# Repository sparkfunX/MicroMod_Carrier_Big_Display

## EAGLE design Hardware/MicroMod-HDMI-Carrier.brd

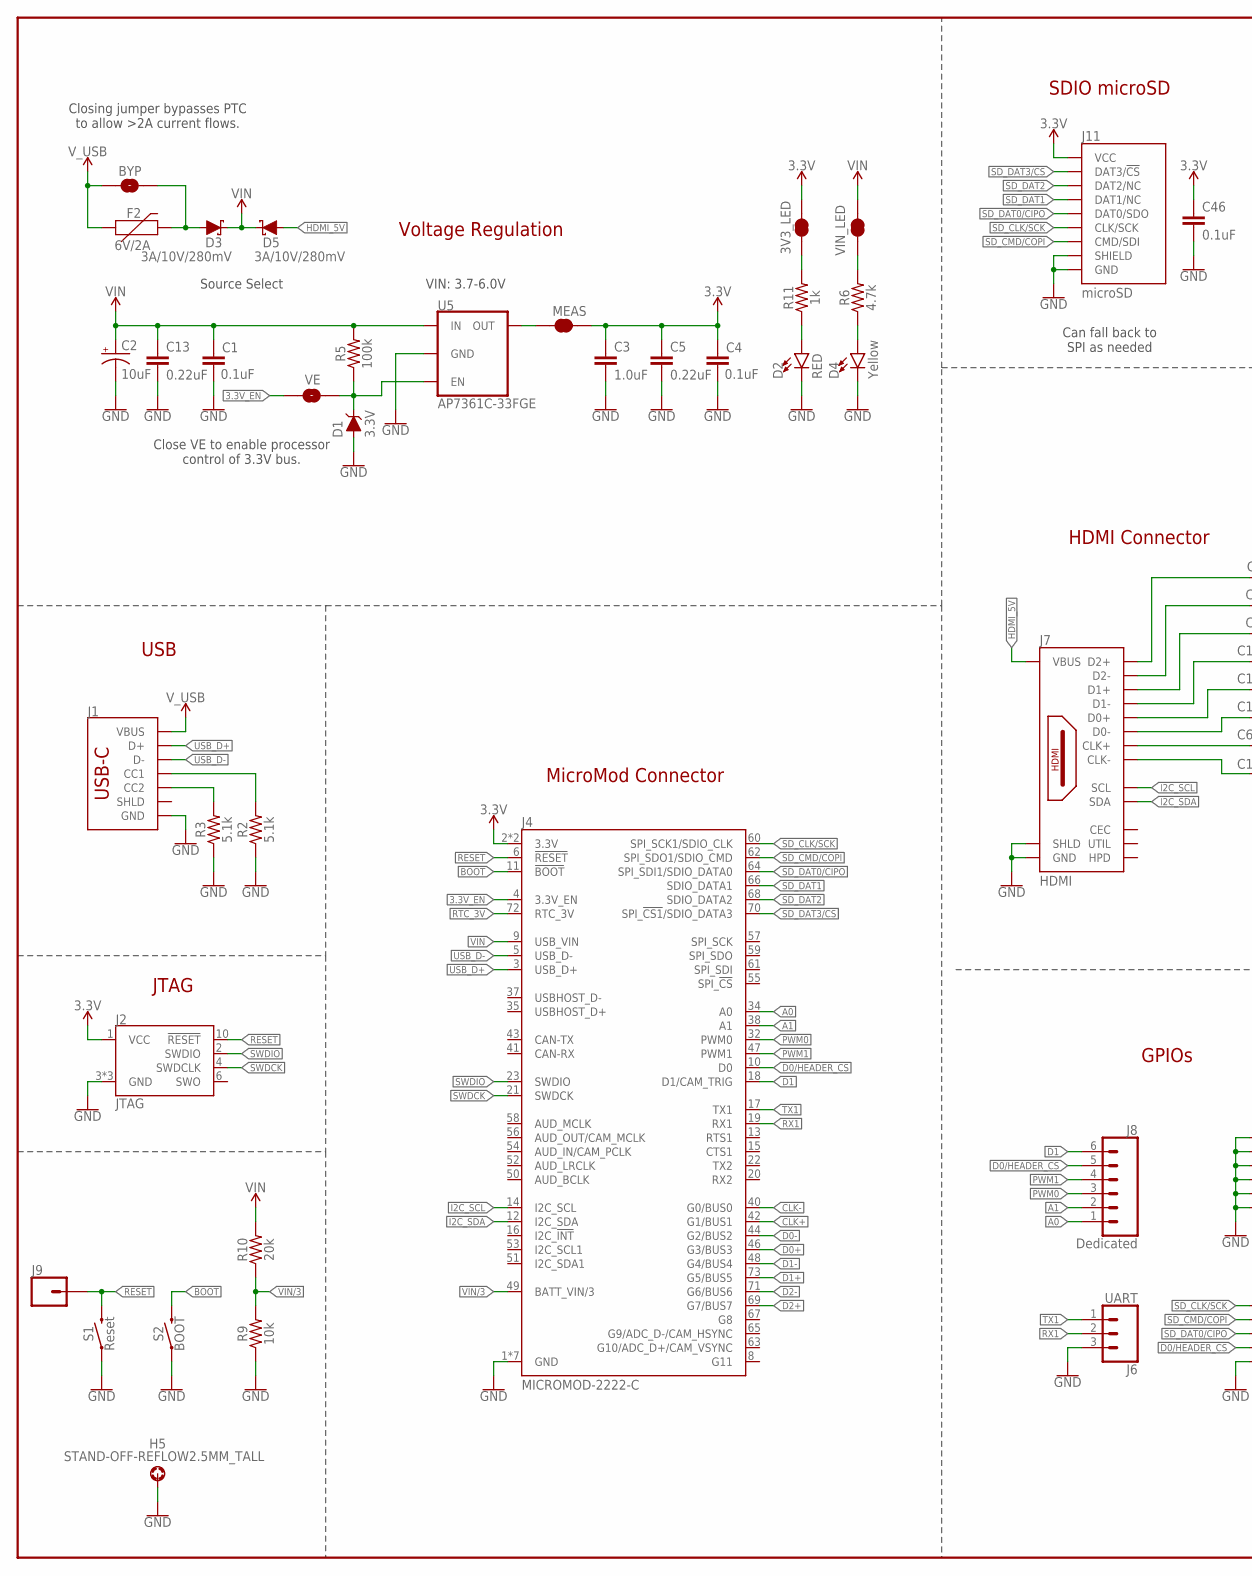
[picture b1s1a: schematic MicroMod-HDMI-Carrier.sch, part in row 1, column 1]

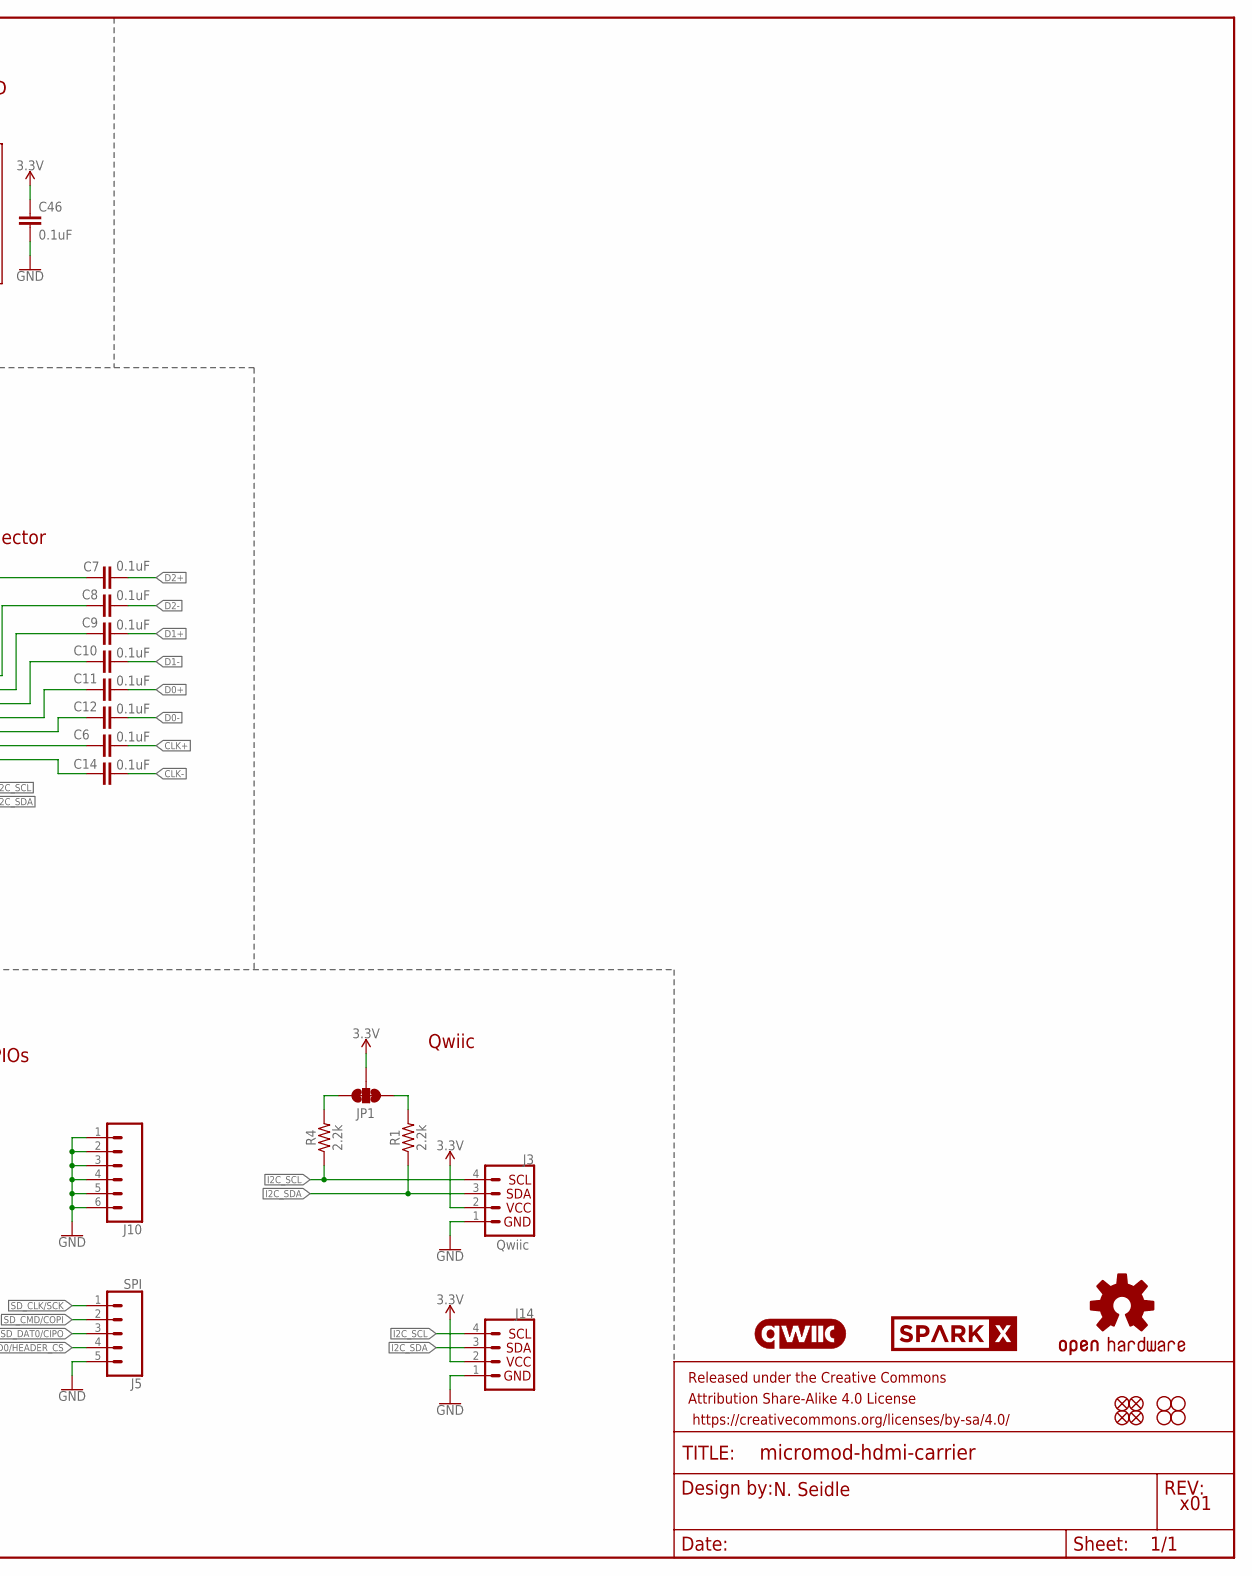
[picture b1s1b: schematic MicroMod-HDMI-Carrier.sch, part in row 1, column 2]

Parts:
3V3_LED: JUMPER-SMT_2_NC_TRACE_SILK; SMT-JUMPER_2_NC_TRACE_SILK
BYP: JUMPER-SMT_2_NO_SILK; SMT-JUMPER_2_NO_SILK
C1, C4, C6, C7, C8, C9, C10, C11, C12, C14, C46: 0.1uF; 0603
C2: 10uF; EIA3216
C3: 1.0uF; 0603
C5, C13: 0.22uF; 0603
D1: 3.3V; SOD-323
D2: RED; LED-0603
D3, D5: 3A/10V/280mV; SOD-323
D4: Yellow; LED-0603
F2: 6V/2A; 1210
FD1, FD2, FD3, FD4: FIDUCIALUFIDUCIAL; FIDUCIAL-MICRO
FRAME1: FRAME-LEDGER; CREATIVE_COMMONS
H1, H2, H3, H4: STAND-OFF
H5: STAND-OFF-REFLOW2.5MM_TALL; STAND-OFF-REFLOW-M2.5
J1: USB_C_2-LAYER_PADS; USB-C-16P-2LAYER-PADS
J2: JTAG; 2X5-PTH-1.27MM
J3: Qwiic; JST04_1MM_RA
J4: MICROMOD-2222-C; M.2-CONNECTOR-E
J5: SPI; 1X05_NO_SILK
J6: UART; 1X03_NO_SILK
J7: HDMI; MOLEX_HDMI_208658-1051
J8: Dedicated; 1X06_NO_SILK
J9: CONN_01PTH_NO_SILK_YES_STOP; 1X01_NO_SILK
J10: CONN_06NO_SILK_NO_POP; 1X06_NO_SILK
J11: microSD; MICRO-SD-SOCKET
J14: I2C_STANDARD_NO_SILK; 1X04_NO_SILK
JP1: JUMPER-SMT_3_2-NC_TRACE_SILK; SMT-JUMPER_3_2-NC_TRACE_SILK
LOGO2: QWIIC_LOGO_CONNECTOR; QWIIC_5.5MM
LOGO3: OSHW-LOGOMINI; OSHW-LOGO-MINI
MEAS: JUMPER-COMBO_2_NC_TRACE; COMBO-JUMPER_2_NC_TRACE
R1, R4: 2.2k; 0603
R2, R3: 5.1k; 0603
R5: 100k; 0603
R6: 4.7k; 0603
R9: 10k; 0603
R10: 20k; 0603
R11: 1k; 0603
S1: Reset; TACTILE_SWITCH_SMD_5.2MM
S2: BOOT; TACTILE_SWITCH_SMD_5.2MM
U5: AP7361C-33FGE; UDFN-8
U$1: SPARKX-LOGO4; SPARKX-MEDIUM
VE: JUMPER-SMT_2_NO_SILK; SMT-JUMPER_2_NO_SILK
VIN_LED: JUMPER-SMT_2_NC_TRACE_SILK; SMT-JUMPER_2_NC_TRACE_SILK

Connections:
3.3V: 3V3_LED.2, C3.1, C4.1, C5.1, C46.1, J2.1 (VCC), J3.2, J4.2 (3.3V), J4.74 (3.3V), J11.VCC, J14.2, JP1.2, MEAS.2, MEAS.4 (2)
3.3V_EN: J4.4 (3.3V_EN), VE.1
!BOOT!: J4.11 (!BOOT!), S2.3 (2), S2.4 (2)
!RESET!: J2.10 (!RESET), J4.6 (!RESET!), J9.1, S1.3 (2), S1.4 (2)
A0: J4.34 (A0), J8.1
A1: J4.38 (A1), J8.2
CLK+: C6.1, J4.42 (G1/BUS1)
CLK-: C14.1, J4.40 (G0/BUS0)
D0+: C11.1, J4.46 (G3/BUS3)
D0-: C12.1, J4.44 (G2/BUS2)
D0/HEADER_!CS!: J4.10 (D0), J5.4, J8.5
D1: J4.18 (D1/CAM_TRIG), J8.6
D1+: C9.1, J4.73 (G5/BUS5)
D1-: C10.1, J4.48 (G4/BUS4)
D2+: C7.1, J4.69 (G7/BUS7)
D2-: C8.1, J4.71 (G6/BUS6)
GND: C1.2, C2.-, C3.2, C4.2, C5.2, C13.2, C46.2, D1.A, D2.C, D4.C, H5.1, J1.GND, J1.GND2 (GND), J2.3 (GND), J2.5 (GND), J2.9 (GND), J3.1, J4.1 (GND), J4.7 (GND), J4.33 (GND), J4.36 (GND), J4.39 (GND), J4.45 (GND), J4.75 (GND), J5.5, J6.3, J7.2 (GND), J7.5 (GND), J7.8 (GND), J7.11 (GND), J7.17 (GND), J7.MH1 (SHLD), J7.MH2 (SHLD), J7.MH3 (SHLD), J7.MH4 (SHLD), J10.1, J10.2, J10.3, J10.4, J10.5, J10.6, J11.CD1 (SHIELD), J11.GND, J11.GND1 (GND), J11.GND3 (GND), J14.1, R2.1, R3.1, R9.1, S1.1, S1.2 (1), S2.1, S2.2 (1), U5.4 (GND), U5.EP (GND)
HDMI_5V: D5.A, J7.18 (VBUS)
I2C_SCL: J3.4, J4.14 (I2C_SCL), J7.15 (SCL), J14.4, R4.1
I2C_SDA: J3.3, J4.12 (I2C_SDA), J7.16 (SDA), J14.3, R1.1
unnamed: R6.2, VIN_LED.1
unnamed: JP1.3, R4.2
unnamed: JP1.1, R1.2
unnamed: C7.2, J7.1 (D2+)
unnamed: C8.2, J7.3 (D2-)
unnamed: 3V3_LED.1, R11.2
unnamed: D2.A, R11.1
unnamed: D4.A, R6.1
unnamed: C9.2, J7.4 (D1+)
unnamed: J1.A5 (CC1), R2.2
unnamed: J1.B5 (CC2), R3.2
unnamed: D1.C, R5.1, U5.5 (EN), VE.2
unnamed: C10.2, J7.6 (D1-)
unnamed: C11.2, J7.7 (D0+)
unnamed: C12.2, J7.9 (D0-)
unnamed: C6.2, J7.10 (CLK+)
unnamed: C14.2, J7.12 (CLK-)
unnamed: BYP.2, D3.A, F2.2
PWM0: J4.32 (PWM0), J8.3
PWM1: J4.47 (PWM1), J8.4
RTC_3V: J4.72 (RTC_3V)
RX1: J4.19 (RX1), J6.2
SD_CLK/SCK: J4.60 (SPI_SCK1/SDIO_CLK), J5.1, J11.SCLK (CLK/SCK)
SD_CMD/COPI: J4.62 (SPI_SDO1/SDIO_CMD), J5.2, J11.DI/CMD (CMD/SDI)
SD_DAT0/CIPO: J4.64 (SPI_SDI1/SDIO_DATA0), J5.3, J11.DO/DAT0 (DAT0/SDO)
SD_DAT1: J4.66 (SDIO_DATA1), J11.DAT1 (DAT1/NC)
SD_DAT2: J4.68 (SDIO_DATA2), J11.DAT2 (DAT2/NC)
SD_DAT3/!CS!: J4.70 (SPI_!CS1!/SDIO_DATA3), J11.CS/DAT3 (DAT3/!CS!)
SWDCK: J2.4 (SWDCLK), J4.21 (SWDCK)
SWDIO: J2.2 (SWDIO), J4.23 (SWDIO)
TX1: J4.17 (TX1), J6.1
USB_D+: J1.A6 (D+), J1.B6 (D+), J4.3 (USB_D+)
USB_D-: J1.A7 (D-), J1.B7 (D-), J4.5 (USB_D-)
VIN: C1.1, C2.+, C13.1, D3.C, D5.C, J4.9 (USB_VIN), R5.2, R10.2, U5.8 (IN), VIN_LED.2
VIN/3: J4.49 (BATT_VIN/3), R9.2, R10.1
VREG_3.3V: MEAS.1, MEAS.3 (1), U5.1 (OUT)
V_USB: BYP.1, F2.1, J1.VBUS1 (VBUS), J1.VBUS2 (VBUS)

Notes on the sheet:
SDIO microSD
Closing jumper bypasses PTC to allow >2A current flows.
JTAG
USB
GPIOs
Qwiic
Voltage Regulation
MicroMod Connector
N. Seidle
x01
VIN: 3.7-6.0V
Close VE to enable processor control of 3.3V bus.
HDMI Connector
Can fall back to SPI as needed
Source Select

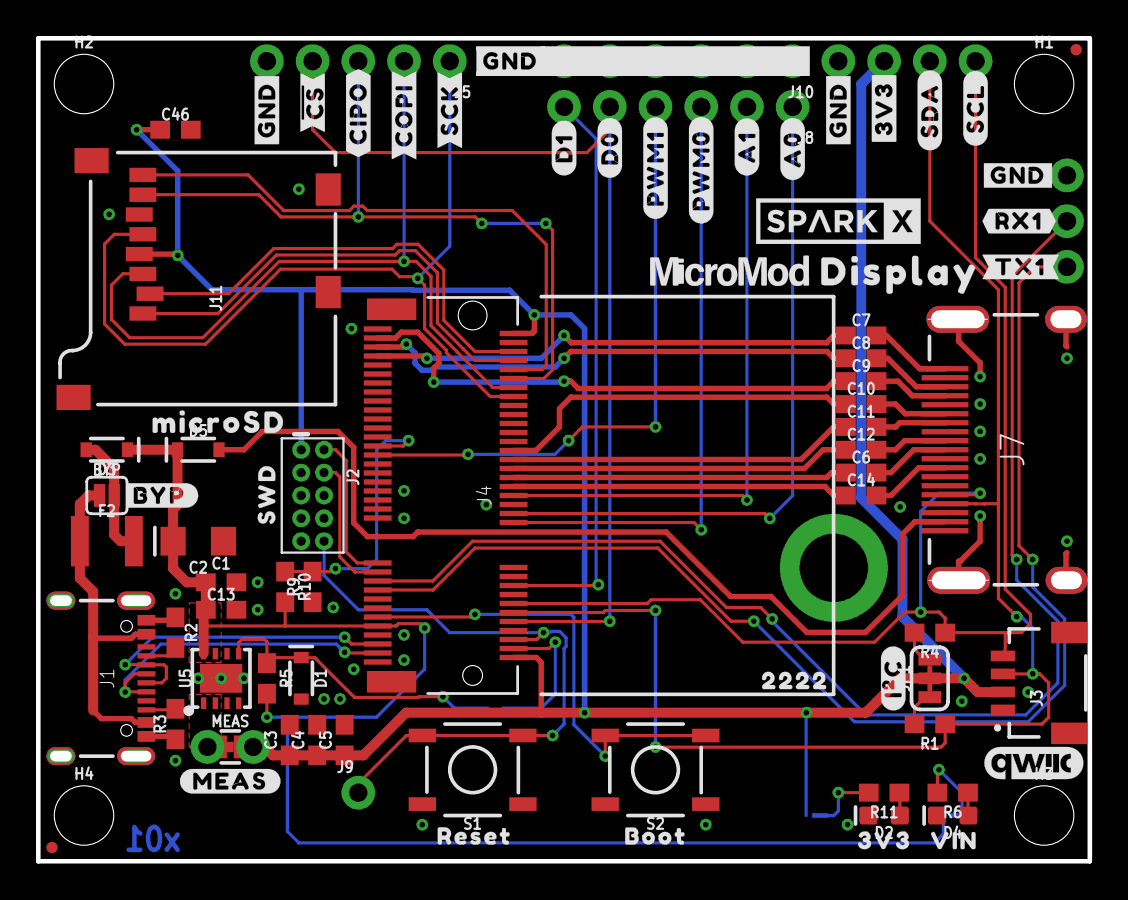
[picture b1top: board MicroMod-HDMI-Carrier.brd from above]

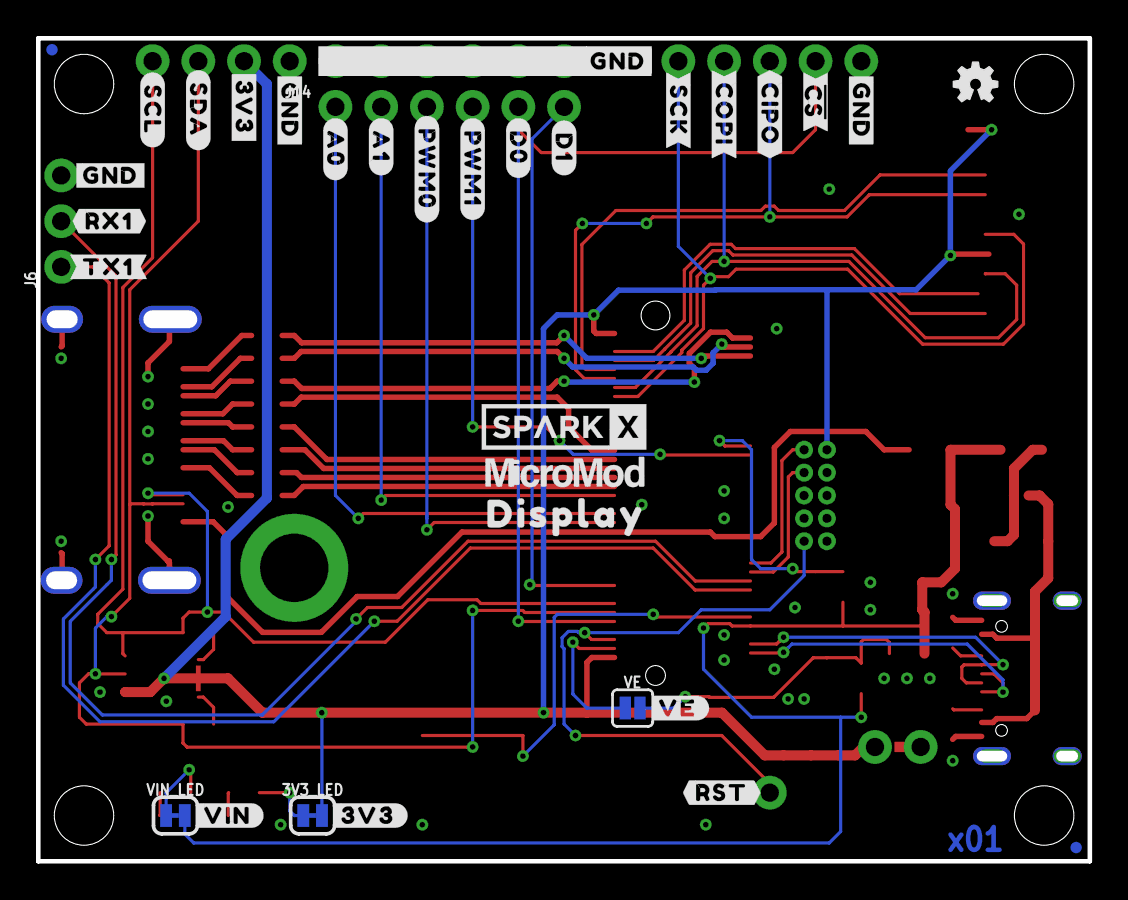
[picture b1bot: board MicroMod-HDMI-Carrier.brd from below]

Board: 2 copper layers, 57.7 x 45.0 mm, 121 parts (34 on the bottom side), 56 nets.

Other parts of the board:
U$2: MICROSD0
U$3, U$5: DISPLAY0
U$4: #3V3#0
U$6, U$7: #A0#5
U$8, U$9: #A1#4
U$10, U$25: #D0#1
U$11, U$12, U$15, U$16: #GND#0
U$13, U$14: #3V3#1
U$17: #RST#1
U$18: #VE#0
U$19: #MEAS#2
U$20: #VIN#1
U$21: SWD0
U$22: SPARKX-LOGO4; SPARKX-MEDIUM
U$23: #I�C#0
U$24, U$34: MICROMOD_LOGO_.35
U$29, U$31: #D1#0
U$32, U$41: #PWM0#3
U$33: #BYP#1
U$35, U$68: ##CS##3
U$36: 3V37
U$38: 22223
U$40: BOOT5
U$42, U$49: #PWM1#2
U$43, U$44: #SCL#3
U$45: RESET6
U$46: VIN8
U$50, U$51: #SDA#2
U$69, U$70: #CIPO#2
U$71, U$72: #COPI#1
U$73, U$74, U$81, U$82: #GND#4
U$75, U$76: #RX1#6
U$77, U$78: #SCK#0
U$79, U$80: #TX1#5

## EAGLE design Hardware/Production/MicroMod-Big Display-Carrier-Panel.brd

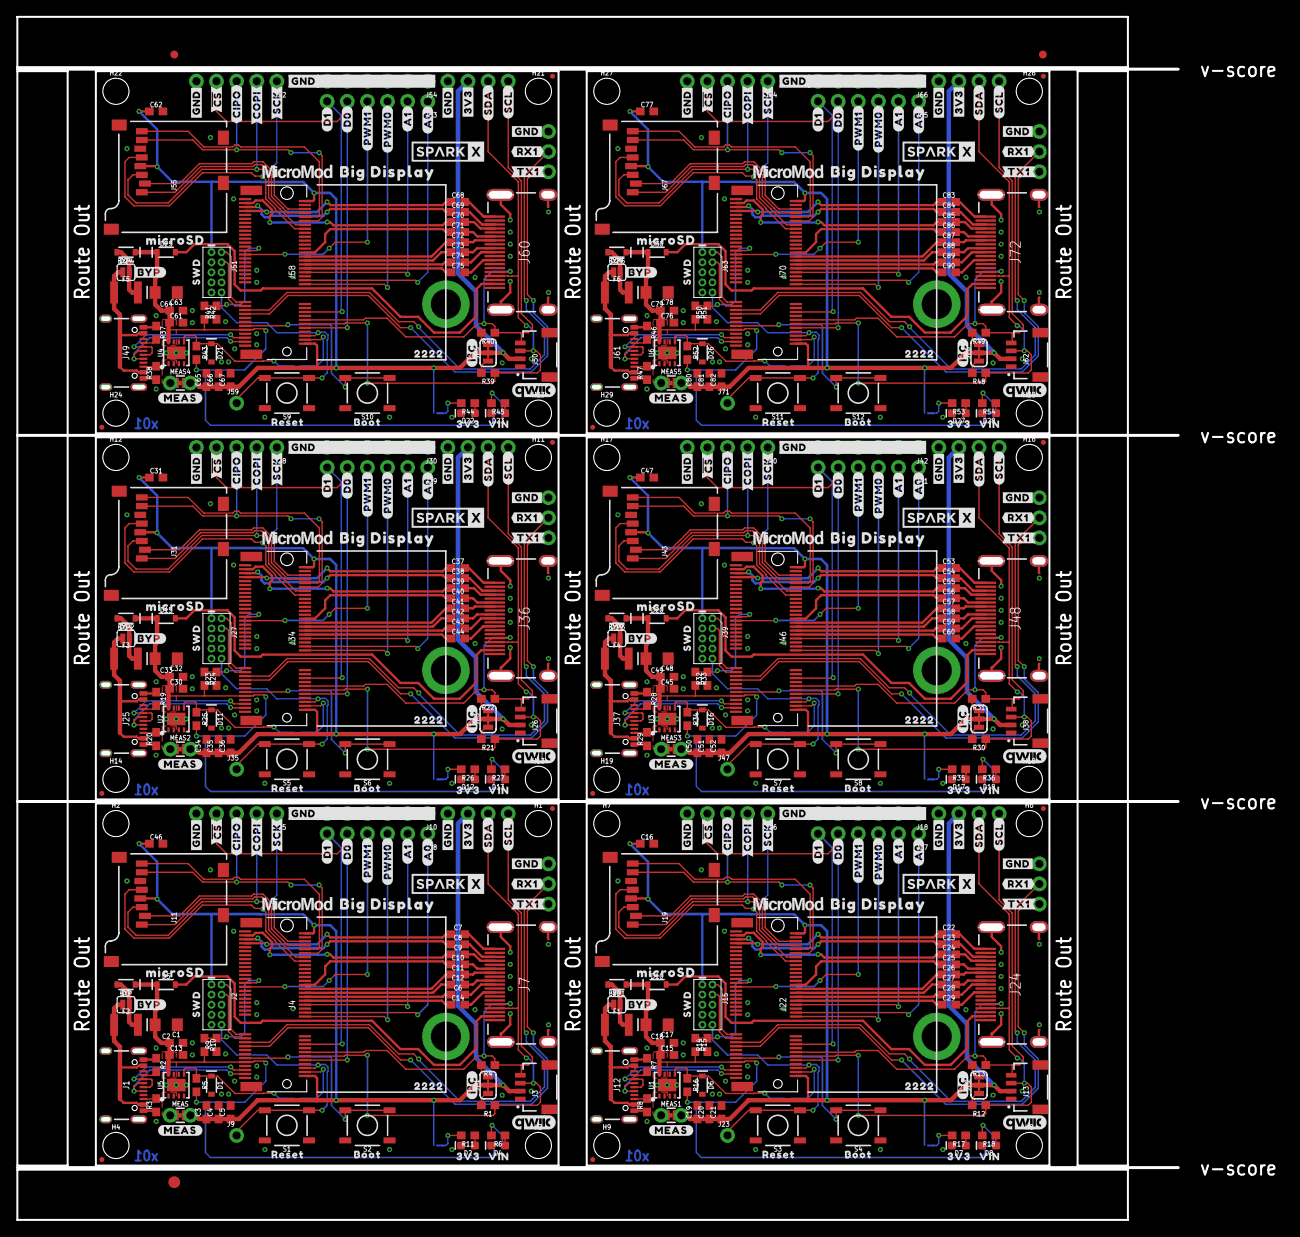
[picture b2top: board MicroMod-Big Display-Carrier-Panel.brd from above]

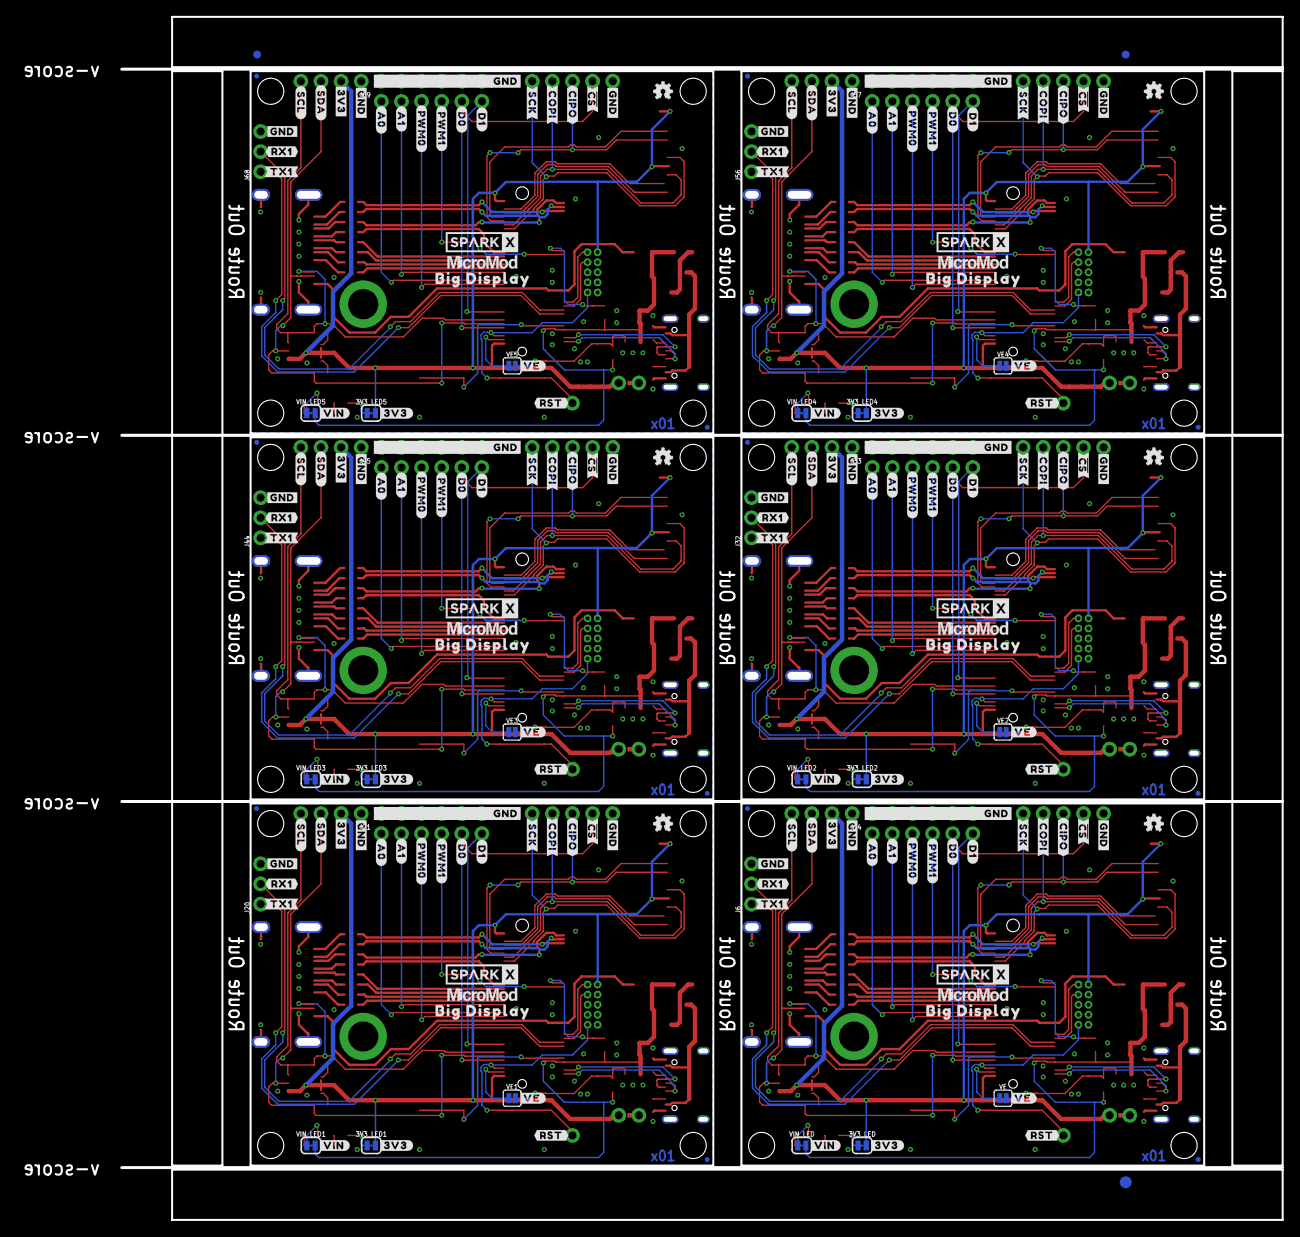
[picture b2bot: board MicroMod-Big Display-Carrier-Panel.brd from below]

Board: 2 copper layers, 159.1 x 151.1 mm, 726 parts (207 on the bottom side), 336 nets.

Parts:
3V3_LED, 3V3_LED1, 3V3_LED2, 3V3_LED3, 3V3_LED4, 3V3_LED5: SMT-JUMPER_2_NC_TRACE_SILK
BYP, BYP1, BYP2, BYP3, BYP4, BYP5: JUMPER-SMT_2_NO_SILK; SMT-JUMPER_2_NO_SILK
C1, C4, C6, C7, C8, C9, C10, C11, C12, C14, C16, C17, C20, C22, C23, C24, C25, C26, C27, C28, C29, C31, C32, C35, C37, C38, C39, C40, C41, C42, C43, C44, C46, C47, C48, C51, C53, C54, C55, C56, C57, C58, C59, C60, C62, C63, C66, C68, C69, C70, C71, C72, C73, C74, C75, C77, C78, C81, C83, C84, C85, C86, C87, C88, C89, C90: 0.1uF; 0603
C2, C18, C33, C49, C64, C79: 10uF; EIA3216
C3, C19, C34, C50, C65, C80: 1.0uF; 0603
C5, C13, C15, C21, C30, C36, C45, C52, C61, C67, C76, C82: 0.22uF; 0603
D1, D6, D11, D16, D21, D26: 3.3V; SOD-323
D2, D7, D12, D17, D22, D27: RED; LED-0603
D3, D5, D9, D10, D14, D15, D19, D20, D24, D25, D29, D30: 3A/10V/280mV; SOD-323
D4, D8, D13, D18, D23, D28: Yellow; LED-0603
E$1, E$2, E$3, E$4: FIDUCIAL-1X2
E$5, E$6: FIDUCIAL-1.5X3
F1, F2, F3, F4, F5, F6: 6V/2A; 1210
FD1, FD2, FD3, FD4, FD5, FD6, FD7, FD8, FD9, FD10, FD11, FD12, FD13, FD14, FD15, FD16, FD17, FD18, FD19, FD20, FD21, FD22, FD23, FD24: FIDUCIALUFIDUCIAL; FIDUCIAL-MICRO
H1, H2, H3, H4, H6, H7, H8, H9, H11, H12, H13, H14, H16, H17, H18, H19, H21, H22, H23, H24, H26, H27, H28, H29: STAND-OFF
H5, H10, H15, H20, H25, H30: STAND-OFF-REFLOW2.5MM_TALL; STAND-OFF-REFLOW-M2.5
J1, J12, J25, J37, J49, J61: USB-C-16P-2LAYER-PADS
J2, J15, J27, J39, J51, J63: JTAG; 2X5-PTH-1.27MM
J3, J13, J26, J38, J50, J62: Qwiic; JST04_1MM_RA
J4, J22, J34, J46, J58, J70: MICROMOD-2222-C; M.2-CONNECTOR-E
J5, J16, J28, J40, J52, J64: SPI; 1X05_NO_SILK
J6, J20, J32, J44, J56, J68: UART; 1X03_NO_SILK
J7, J24, J36, J48, J60, J72: HDMI; MOLEX_HDMI_208658-1051
J8, J17, J29, J41, J53, J65: Dedicated; 1X06_NO_SILK
J9, J23, J35, J47, J59, J71: 1X01_NO_SILK
J10, J18, J30, J42, J54, J66: 1X06_NO_SILK
J11, J19, J31, J43, J55, J67: microSD; MICRO-SD-SOCKET
J14, J21, J33, J45, J57, J69: 1X04_NO_SILK
JP1, JP2, JP3, JP4, JP5, JP6: SMT-JUMPER_3_2-NC_TRACE_SILK
LOGO1, LOGO2, LOGO5, LOGO7, LOGO9, LOGO11: QWIIC_LOGO_CONNECTOR; QWIIC_5.5MM
LOGO3, LOGO4, LOGO6, LOGO8, LOGO10, LOGO12: OSHW-LOGOMINI; OSHW-LOGO-MINI
MEAS, MEAS1, MEAS2, MEAS3, MEAS4, MEAS5: COMBO-JUMPER_2_NC_TRACE
R1, R4, R12, R13, R21, R22, R30, R31, R39, R40, R48, R49: 2.2k; 0603
R2, R3, R7, R8, R19, R20, R28, R29, R37, R38, R46, R47: 5.1k; 0603
R5, R16, R25, R34, R43, R52: 100k; 0603
R6, R18, R27, R36, R45, R54: 4.7k; 0603
R9, R14, R23, R32, R41, R50: 10k; 0603
R10, R15, R24, R33, R42, R51: 20k; 0603
R11, R17, R26, R35, R44, R53: 1k; 0603
S1, S3, S5, S7, S9, S11: Reset; TACTILE_SWITCH_SMD_5.2MM
S2, S4, S6, S8, S10, S12: BOOT; TACTILE_SWITCH_SMD_5.2MM
U1, U2, U3, U4, U5, U6: AP7361C-33FGE; UDFN-8
U$1, U$22, U$113, U$114, U$171, U$172, U$229, U$230, U$287, U$288, U$345, U$346: SPARKX-LOGO4; SPARKX-MEDIUM
U$2, U$112, U$170, U$228, U$286, U$344: MICROSD0
U$3, U$5, U$115, U$116, U$173, U$174, U$231, U$232, U$289, U$290, U$347, U$348: BIG_DISPLAY0
U$4, U$110, U$168, U$226, U$284, U$342: #3V3#0
U$6, U$7, U$62, U$63, U$135, U$136, U$193, U$194, U$251, U$252, U$309, U$310: #A0#5
U$8, U$9, U$64, U$65, U$137, U$138, U$195, U$196, U$253, U$254, U$311, U$312: #A1#4
U$10, U$25, U$66, U$67, U$139, U$140, U$197, U$198, U$255, U$256, U$313, U$314: #D0#1
U$11, U$12, U$15, U$16, U$89, U$90, U$93, U$94, U$147, U$148, U$151, U$152, U$205, U$206, U$209, U$210, U$263, U$264, U$267, U$268, U$321, U$322, U$325, U$326: #GND#0
U$13, U$14, U$91, U$92, U$149, U$150, U$207, U$208, U$265, U$266, U$323, U$324: #3V3#1
U$17, U$107, U$165, U$223, U$281, U$339: #RST#1
U$18, U$108, U$166, U$224, U$282, U$340: #VE#0
U$19, U$104, U$162, U$220, U$278, U$336: #MEAS#2
U$20, U$111, U$169, U$227, U$285, U$343: #VIN#1
U$21, U$105, U$163, U$221, U$279, U$337: SWD0
U$23, U$109, U$167, U$225, U$283, U$341: #I�C#0
U$24, U$26, U$27, U$34, U$117, U$118, U$175, U$176, U$233, U$234, U$291, U$292: MICROMOD_LOGO_.35
U$28, U$30, U$35, U$68, U$119, U$120, U$177, U$178, U$235, U$236, U$293, U$294: ##CS##3
U$29, U$31, U$83, U$84, U$141, U$142, U$199, U$200, U$257, U$258, U$315, U$316: #D1#0
U$32, U$41, U$85, U$86, U$143, U$144, U$201, U$202, U$259, U$260, U$317, U$318: #PWM0#3
U$33, U$106, U$164, U$222, U$280, U$338: #BYP#1
U$36, U$99, U$157, U$215, U$273, U$331: 3V37
U$37, U$39, U$69, U$70, U$121, U$122, U$179, U$180, U$237, U$238, U$295, U$296: #CIPO#2
U$38, U$100, U$158, U$216, U$274, U$332: 22223
U$40, U$101, U$159, U$217, U$275, U$333: BOOT5
U$42, U$49, U$87, U$88, U$145, U$146, U$203, U$204, U$261, U$262, U$319, U$320: #PWM1#2
U$43, U$44, U$95, U$96, U$153, U$154, U$211, U$212, U$269, U$270, U$327, U$328: #SCL#3
U$45, U$102, U$160, U$218, U$276, U$334: RESET6
U$46, U$103, U$161, U$219, U$277, U$335: VIN8
U$47, U$48, U$71, U$72, U$123, U$124, U$181, U$182, U$239, U$240, U$297, U$298: #COPI#1
U$50, U$51, U$97, U$98, U$155, U$156, U$213, U$214, U$271, U$272, U$329, U$330: #SDA#2
U$52, U$53, U$60, U$61, U$73, U$74, U$81, U$82, U$125, U$126, U$133, U$134, U$183, U$184, U$191, U$192, U$241, U$242, U$249, U$250, U$299, U$300, U$307, U$308: #GND#4
U$54, U$55, U$75, U$76, U$127, U$128, U$185, U$186, U$243, U$244, U$301, U$302: #RX1#6
U$56, U$57, U$77, U$78, U$129, U$130, U$187, U$188, U$245, U$246, U$303, U$304: #SCK#0
U$58, U$59, U$79, U$80, U$131, U$132, U$189, U$190, U$247, U$248, U$305, U$306: #TX1#5
VE, VE1, VE2, VE3, VE4, VE5: SMT-JUMPER_2_NO_SILK
VIN_LED, VIN_LED1, VIN_LED2, VIN_LED3, VIN_LED4, VIN_LED5: SMT-JUMPER_2_NC_TRACE_SILK

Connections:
3.3V: 3V3_LED.2, C3.1, C4.1, C5.1, C46.1, J2.1, J3.2, J4.2, J4.74, J11.VCC, J14.2, JP1.2, MEAS.2, MEAS.4
3.3V1: 3V3_LED1.2, C16.1, C19.1, C20.1, C21.1, J13.2, J15.1, J19.VCC, J21.2, J22.2, J22.74, JP2.2, MEAS1.2, MEAS1.4
3.3V2: 3V3_LED2.2, C31.1, C34.1, C35.1, C36.1, J26.2, J27.1, J31.VCC, J33.2, J34.2, J34.74, JP3.2, MEAS2.2, MEAS2.4
3.3V3: 3V3_LED3.2, C47.1, C50.1, C51.1, C52.1, J38.2, J39.1, J43.VCC, J45.2, J46.2, J46.74, JP4.2, MEAS3.2, MEAS3.4
3.3V4: 3V3_LED4.2, C62.1, C65.1, C66.1, C67.1, J50.2, J51.1, J55.VCC, J57.2, J58.2, J58.74, JP5.2, MEAS4.2, MEAS4.4
3.3V5: 3V3_LED5.2, C77.1, C80.1, C81.1, C82.1, J62.2, J63.1, J67.VCC, J69.2, J70.2, J70.74, JP6.2, MEAS5.2, MEAS5.4
3.3V_EN: J4.4, VE.1
3.3V_EN1: J22.4, VE1.1
3.3V_EN2: J34.4, VE2.1
3.3V_EN3: J46.4, VE3.1
3.3V_EN4: J58.4, VE4.1
3.3V_EN5: J70.4, VE5.1
!BOOT!: J4.11, S2.3, S2.4
!BOOT!1: J22.11, S4.3, S4.4
!BOOT!2: J34.11, S6.3, S6.4
!BOOT!3: J46.11, S8.3, S8.4
!BOOT!4: J58.11, S10.3, S10.4
!BOOT!5: J70.11, S12.3, S12.4
!RESET!: J2.10, J4.6, J9.1, S1.3, S1.4
!RESET!1: J15.10, J22.6, J23.1, S3.3, S3.4
!RESET!2: J27.10, J34.6, J35.1, S5.3, S5.4
!RESET!3: J39.10, J46.6, J47.1, S7.3, S7.4
!RESET!4: J51.10, J58.6, J59.1, S9.3, S9.4
!RESET!5: J63.10, J70.6, J71.1, S11.3, S11.4
A0: J4.34, J8.1
A1: J4.38, J8.2
A2: J17.1, J22.34
A3: J17.2, J22.38
A4: J29.1, J34.34
A5: J29.2, J34.38
A6: J41.1, J46.34
A7: J41.2, J46.38
A8: J53.1, J58.34
A9: J53.2, J58.38
A10: J65.1, J70.34
A11: J65.2, J70.38
CLK+: C6.1, J4.42
CLK+1: C28.1, J22.42
CLK+2: C43.1, J34.42
CLK+3: C59.1, J46.42
CLK+4: C74.1, J58.42
CLK+5: C89.1, J70.42
CLK-: C14.1, J4.40
CLK-1: C29.1, J22.40
CLK-2: C44.1, J34.40
CLK-3: C60.1, J46.40
CLK-4: C75.1, J58.40
CLK-5: C90.1, J70.40
D0+: C11.1, J4.46
D0+1: C26.1, J22.46
D0+2: C41.1, J34.46
D0+3: C57.1, J46.46
D0+4: C72.1, J58.46
D0+5: C87.1, J70.46
D0-: C12.1, J4.44
D0-1: C27.1, J22.44
D0-2: C42.1, J34.44
D0-3: C58.1, J46.44
D0-4: C73.1, J58.44
D0-5: C88.1, J70.44
D0/HEADER_!CS!: J4.10, J5.4, J8.5
D0/HEADER_!CS!1: J16.4, J17.5, J22.10
D0/HEADER_!CS!2: J28.4, J29.5, J34.10
D0/HEADER_!CS!3: J40.4, J41.5, J46.10
D0/HEADER_!CS!4: J52.4, J53.5, J58.10
D0/HEADER_!CS!5: J64.4, J65.5, J70.10
D1: J4.18, J8.6
D1+: C9.1, J4.73
D1+1: C24.1, J22.73
D1+2: C39.1, J34.73
D1+3: C55.1, J46.73
D1+4: C70.1, J58.73
D1+5: C85.1, J70.73
D1-: C10.1, J4.48
D1-1: C25.1, J22.48
D1-2: C40.1, J34.48
D1-3: C56.1, J46.48
D1-4: C71.1, J58.48
D1-5: C86.1, J70.48
D2: J17.6, J22.18
D2+: C7.1, J4.69
D2+1: C22.1, J22.69
D2+2: C37.1, J34.69
D2+3: C53.1, J46.69
D2+4: C68.1, J58.69
D2+5: C83.1, J70.69
D2-: C8.1, J4.71
D2-1: C23.1, J22.71
D2-2: C38.1, J34.71
D2-3: C54.1, J46.71
D2-4: C69.1, J58.71
D2-5: C84.1, J70.71
D3: J29.6, J34.18
D4: J41.6, J46.18
D5: J53.6, J58.18
D6: J65.6, J70.18
GND: C1.2, C2.-, C3.2, C4.2, C5.2, C13.2, C46.2, D1.A, D2.C, D4.C, H5.1, J1.GND, J1.GND2, J2.3, J2.5, J2.9, J3.1, J4.1, J4.7, J4.33, J4.36, J4.39, J4.45, J4.75, J5.5, J6.3, J7.2, J7.5, J7.8, J7.11, J7.17, J7.MH1, J7.MH2, J7.MH3, J7.MH4, J10.1, J10.2, J10.3, J10.4, J10.5, J10.6, J11.CD1, J11.GND, J11.GND1, J11.GND3, J14.1, R2.1, R3.1, R9.1, S1.1, S1.2, S2.1, S2.2, U5.4, U5.EP
GND1: C15.2, C16.2, C17.2, C18.-, C19.2, C20.2, C21.2, D6.A, D7.C, D8.C, H10.1, J12.GND, J12.GND2, J13.1, J15.3, J15.5, J15.9, J16.5, J18.1, J18.2, J18.3, J18.4, J18.5, J18.6, J19.CD1, J19.GND, J19.GND1, J19.GND3, J20.3, J21.1, J22.1, J22.7, J22.33, J22.36, J22.39, J22.45, J22.75, J24.2, J24.5, J24.8, J24.11, J24.17, J24.MH1, J24.MH2, J24.MH3, J24.MH4, R7.1, R8.1, R14.1, S3.1, S3.2, S4.1, S4.2, U1.4, U1.EP
GND2: C30.2, C31.2, C32.2, C33.-, C34.2, C35.2, C36.2, D11.A, D12.C, D13.C, H15.1, J25.GND, J25.GND2, J26.1, J27.3, J27.5, J27.9, J28.5, J30.1, J30.2, J30.3, J30.4, J30.5, J30.6, J31.CD1, J31.GND, J31.GND1, J31.GND3, J32.3, J33.1, J34.1, J34.7, J34.33, J34.36, J34.39, J34.45, J34.75, J36.2, J36.5, J36.8, J36.11, J36.17, J36.MH1, J36.MH2, J36.MH3, J36.MH4, R19.1, R20.1, R23.1, S5.1, S5.2, S6.1, S6.2, U2.4, U2.EP
GND3: C45.2, C47.2, C48.2, C49.-, C50.2, C51.2, C52.2, D16.A, D17.C, D18.C, H20.1, J37.GND, J37.GND2, J38.1, J39.3, J39.5, J39.9, J40.5, J42.1, J42.2, J42.3, J42.4, J42.5, J42.6, J43.CD1, J43.GND, J43.GND1, J43.GND3, J44.3, J45.1, J46.1, J46.7, J46.33, J46.36, J46.39, J46.45, J46.75, J48.2, J48.5, J48.8, J48.11, J48.17, J48.MH1, J48.MH2, J48.MH3, J48.MH4, R28.1, R29.1, R32.1, S7.1, S7.2, S8.1, S8.2, U3.4, U3.EP
GND4: C61.2, C62.2, C63.2, C64.-, C65.2, C66.2, C67.2, D21.A, D22.C, D23.C, H25.1, J49.GND, J49.GND2, J50.1, J51.3, J51.5, J51.9, J52.5, J54.1, J54.2, J54.3, J54.4, J54.5, J54.6, J55.CD1, J55.GND, J55.GND1, J55.GND3, J56.3, J57.1, J58.1, J58.7, J58.33, J58.36, J58.39, J58.45, J58.75, J60.2, J60.5, J60.8, J60.11, J60.17, J60.MH1, J60.MH2, J60.MH3, J60.MH4, R37.1, R38.1, R41.1, S9.1, S9.2, S10.1, S10.2, U4.4, U4.EP
GND5: C76.2, C77.2, C78.2, C79.-, C80.2, C81.2, C82.2, D26.A, D27.C, D28.C, H30.1, J61.GND, J61.GND2, J62.1, J63.3, J63.5, J63.9, J64.5, J66.1, J66.2, J66.3, J66.4, J66.5, J66.6, J67.CD1, J67.GND, J67.GND1, J67.GND3, J68.3, J69.1, J70.1, J70.7, J70.33, J70.36, J70.39, J70.45, J70.75, J72.2, J72.5, J72.8, J72.11, J72.17, J72.MH1, J72.MH2, J72.MH3, J72.MH4, R46.1, R47.1, R50.1, S11.1, S11.2, S12.1, S12.2, U6.4, U6.EP
HDMI_5V: D5.A, J7.18
HDMI_5V1: D10.A, J24.18
HDMI_5V2: D15.A, J36.18
HDMI_5V3: D20.A, J48.18
HDMI_5V4: D25.A, J60.18
HDMI_5V5: D30.A, J72.18
I2C_SCL: J3.4, J4.14, J7.15, J14.4, R4.1
I2C_SCL1: J13.4, J21.4, J22.14, J24.15, R13.1
I2C_SCL2: J26.4, J33.4, J34.14, J36.15, R22.1
I2C_SCL3: J38.4, J45.4, J46.14, J48.15, R31.1
I2C_SCL4: J50.4, J57.4, J58.14, J60.15, R40.1
I2C_SCL5: J62.4, J69.4, J70.14, J72.15, R49.1
I2C_SDA: J3.3, J4.12, J7.16, J14.3, R1.1
I2C_SDA1: J13.3, J21.3, J22.12, J24.16, R12.1
I2C_SDA2: J26.3, J33.3, J34.12, J36.16, R21.1
I2C_SDA3: J38.3, J45.3, J46.12, J48.16, R30.1
I2C_SDA4: J50.3, J57.3, J58.12, J60.16, R39.1
I2C_SDA5: J62.3, J69.3, J70.12, J72.16, R48.1
unnamed: R6.2, VIN_LED.1
unnamed: JP1.3, R4.2
unnamed: JP1.1, R1.2
unnamed: C7.2, J7.1
unnamed: C8.2, J7.3
unnamed: 3V3_LED.1, R11.2
unnamed: D2.A, R11.1
unnamed: D4.A, R6.1
unnamed: C9.2, J7.4
unnamed: J1.A5, R2.2
unnamed: J1.B5, R3.2
unnamed: D1.C, R5.1, U5.5, VE.2
unnamed: C10.2, J7.6
unnamed: C11.2, J7.7
unnamed: C12.2, J7.9
unnamed: C6.2, J7.10
unnamed: C14.2, J7.12
unnamed: BYP.2, D3.A, F2.2
unnamed: J12.A5, R7.2
unnamed: J12.B5, R8.2
unnamed: JP2.3, R13.2
unnamed: JP2.1, R12.2
unnamed: 3V3_LED1.1, R17.2
unnamed: D7.A, R17.1
unnamed: R18.2, VIN_LED1.1
unnamed: D8.A, R18.1
unnamed: D6.C, R16.1, U1.5, VE1.2
unnamed: C22.2, J24.1
unnamed: C23.2, J24.3
unnamed: C24.2, J24.4
unnamed: C25.2, J24.6
unnamed: C28.2, J24.10
unnamed: C29.2, J24.12
unnamed: C26.2, J24.7
unnamed: C27.2, J24.9
unnamed: BYP1.2, D9.A, F1.2
unnamed: J25.A5, R19.2
unnamed: J25.B5, R20.2
unnamed: JP3.3, R22.2
unnamed: JP3.1, R21.2
unnamed: 3V3_LED2.1, R26.2
unnamed: D12.A, R26.1
unnamed: R27.2, VIN_LED2.1
unnamed: D13.A, R27.1
unnamed: D11.C, R25.1, U2.5, VE2.2
unnamed: C37.2, J36.1
unnamed: C38.2, J36.3
unnamed: C39.2, J36.4
unnamed: C40.2, J36.6
unnamed: C43.2, J36.10
unnamed: C44.2, J36.12
unnamed: C41.2, J36.7
unnamed: C42.2, J36.9
unnamed: BYP2.2, D14.A, F3.2
unnamed: J37.A5, R28.2
unnamed: J37.B5, R29.2
unnamed: JP4.3, R31.2
unnamed: JP4.1, R30.2
unnamed: 3V3_LED3.1, R35.2
unnamed: D17.A, R35.1
unnamed: R36.2, VIN_LED3.1
unnamed: D18.A, R36.1
unnamed: D16.C, R34.1, U3.5, VE3.2
unnamed: C53.2, J48.1
unnamed: C54.2, J48.3
unnamed: C55.2, J48.4
unnamed: C56.2, J48.6
unnamed: C59.2, J48.10
unnamed: C60.2, J48.12
unnamed: C57.2, J48.7
unnamed: C58.2, J48.9
unnamed: BYP3.2, D19.A, F4.2
unnamed: J49.A5, R37.2
unnamed: J49.B5, R38.2
unnamed: JP5.3, R40.2
unnamed: JP5.1, R39.2
unnamed: 3V3_LED4.1, R44.2
unnamed: D22.A, R44.1
unnamed: R45.2, VIN_LED4.1
unnamed: D23.A, R45.1
unnamed: D21.C, R43.1, U4.5, VE4.2
unnamed: C68.2, J60.1
unnamed: C69.2, J60.3
unnamed: C70.2, J60.4
unnamed: C71.2, J60.6
unnamed: C74.2, J60.10
unnamed: C75.2, J60.12
unnamed: C72.2, J60.7
unnamed: C73.2, J60.9
unnamed: BYP4.2, D24.A, F5.2
unnamed: J61.A5, R46.2
unnamed: J61.B5, R47.2
unnamed: JP6.3, R49.2
unnamed: JP6.1, R48.2
unnamed: 3V3_LED5.1, R53.2
unnamed: D27.A, R53.1
unnamed: R54.2, VIN_LED5.1
unnamed: D28.A, R54.1
unnamed: D26.C, R52.1, U6.5, VE5.2
unnamed: C83.2, J72.1
unnamed: C84.2, J72.3
unnamed: C85.2, J72.4
unnamed: C86.2, J72.6
unnamed: C89.2, J72.10
unnamed: C90.2, J72.12
unnamed: C87.2, J72.7
unnamed: C88.2, J72.9
unnamed: BYP5.2, D29.A, F6.2
PWM0: J4.32, J8.3
PWM1: J4.47, J8.4
PWM2: J17.3, J22.32
PWM3: J17.4, J22.47
PWM4: J29.3, J34.32
PWM5: J29.4, J34.47
PWM6: J41.3, J46.32
PWM7: J41.4, J46.47
PWM8: J53.3, J58.32
PWM9: J53.4, J58.47
PWM10: J65.3, J70.32
PWM11: J65.4, J70.47
RX1: J4.19, J6.2
RX2: J20.2, J22.19
RX3: J32.2, J34.19
RX4: J44.2, J46.19
RX5: J56.2, J58.19
RX6: J68.2, J70.19
SD_CLK/SCK: J4.60, J5.1, J11.SCLK
SD_CLK/SCK1: J16.1, J19.SCLK, J22.60
SD_CLK/SCK2: J28.1, J31.SCLK, J34.60
SD_CLK/SCK3: J40.1, J43.SCLK, J46.60
SD_CLK/SCK4: J52.1, J55.SCLK, J58.60
SD_CLK/SCK5: J64.1, J67.SCLK, J70.60
SD_CMD/COPI: J4.62, J5.2, J11.DI/CMD
SD_CMD/COPI1: J16.2, J19.DI/CMD, J22.62
SD_CMD/COPI2: J28.2, J31.DI/CMD, J34.62
SD_CMD/COPI3: J40.2, J43.DI/CMD, J46.62
SD_CMD/COPI4: J52.2, J55.DI/CMD, J58.62
SD_CMD/COPI5: J64.2, J67.DI/CMD, J70.62
SD_DAT0/CIPO: J4.64, J5.3, J11.DO/DAT0
SD_DAT0/CIPO1: J16.3, J19.DO/DAT0, J22.64
SD_DAT0/CIPO2: J28.3, J31.DO/DAT0, J34.64
SD_DAT0/CIPO3: J40.3, J43.DO/DAT0, J46.64
SD_DAT0/CIPO4: J52.3, J55.DO/DAT0, J58.64
SD_DAT0/CIPO5: J64.3, J67.DO/DAT0, J70.64
SD_DAT1: J4.66, J11.DAT1
SD_DAT2: J4.68, J11.DAT2
SD_DAT3: J19.DAT1, J22.66
SD_DAT3/!CS!: J4.70, J11.CS/DAT3
SD_DAT3/!CS!1: J19.CS/DAT3, J22.70
SD_DAT3/!CS!2: J31.CS/DAT3, J34.70
SD_DAT3/!CS!3: J43.CS/DAT3, J46.70
SD_DAT3/!CS!4: J55.CS/DAT3, J58.70
SD_DAT3/!CS!5: J67.CS/DAT3, J70.70
SD_DAT4: J19.DAT2, J22.68
SD_DAT5: J31.DAT1, J34.66
SD_DAT6: J31.DAT2, J34.68
SD_DAT7: J43.DAT1, J46.66
SD_DAT8: J43.DAT2, J46.68
SD_DAT9: J55.DAT1, J58.66
SD_DAT10: J55.DAT2, J58.68
SD_DAT11: J67.DAT1, J70.66
SD_DAT12: J67.DAT2, J70.68
SWDCK: J2.4, J4.21
SWDCK1: J15.4, J22.21
SWDCK2: J27.4, J34.21
SWDCK3: J39.4, J46.21
SWDCK4: J51.4, J58.21
SWDCK5: J63.4, J70.21
SWDIO: J2.2, J4.23
SWDIO1: J15.2, J22.23
SWDIO2: J27.2, J34.23
SWDIO3: J39.2, J46.23
SWDIO4: J51.2, J58.23
SWDIO5: J63.2, J70.23
TX1: J4.17, J6.1
TX2: J20.1, J22.17
TX3: J32.1, J34.17
TX4: J44.1, J46.17
TX5: J56.1, J58.17
TX6: J68.1, J70.17
USB_D+: J1.A6, J1.B6, J4.3
USB_D+1: J12.A6, J12.B6, J22.3
USB_D+2: J25.A6, J25.B6, J34.3
USB_D+3: J37.A6, J37.B6, J46.3
USB_D+4: J49.A6, J49.B6, J58.3
USB_D+5: J61.A6, J61.B6, J70.3
USB_D-: J1.A7, J1.B7, J4.5
USB_D-1: J12.A7, J12.B7, J22.5
USB_D-2: J25.A7, J25.B7, J34.5
USB_D-3: J37.A7, J37.B7, J46.5
USB_D-4: J49.A7, J49.B7, J58.5
USB_D-5: J61.A7, J61.B7, J70.5
VIN: C1.1, C2.+, C13.1, D3.C, D5.C, J4.9, R5.2, R10.2, U5.8, VIN_LED.2
VIN1: C15.1, C17.1, C18.+, D9.C, D10.C, J22.9, R15.2, R16.2, U1.8, VIN_LED1.2
VIN2: C30.1, C32.1, C33.+, D14.C, D15.C, J34.9, R24.2, R25.2, U2.8, VIN_LED2.2
VIN3: C45.1, C48.1, C49.+, D19.C, D20.C, J46.9, R33.2, R34.2, U3.8, VIN_LED3.2
VIN4: C61.1, C63.1, C64.+, D24.C, D25.C, J58.9, R42.2, R43.2, U4.8, VIN_LED4.2
VIN5: C76.1, C78.1, C79.+, D29.C, D30.C, J70.9, R51.2, R52.2, U6.8, VIN_LED5.2
VIN/1: J22.49, R14.2, R15.1
VIN/2: J34.49, R23.2, R24.1
VIN/3: J4.49, R9.2, R10.1
VIN/4: J46.49, R32.2, R33.1
VIN/5: J58.49, R41.2, R42.1
VIN/6: J70.49, R50.2, R51.1
VREG_3.3V: MEAS.1, MEAS.3, U5.1
VREG_3.3V1: MEAS1.1, MEAS1.3, U1.1
VREG_3.3V2: MEAS2.1, MEAS2.3, U2.1
VREG_3.3V3: MEAS3.1, MEAS3.3, U3.1
VREG_3.3V4: MEAS4.1, MEAS4.3, U4.1
VREG_3.3V5: MEAS5.1, MEAS5.3, U6.1
V_USB: BYP.1, F2.1, J1.VBUS1, J1.VBUS2
V_USB1: BYP1.1, F1.1, J12.VBUS1, J12.VBUS2
V_USB2: BYP2.1, F3.1, J25.VBUS1, J25.VBUS2
V_USB3: BYP3.1, F4.1, J37.VBUS1, J37.VBUS2
V_USB4: BYP4.1, F5.1, J49.VBUS1, J49.VBUS2
V_USB5: BYP5.1, F6.1, J61.VBUS1, J61.VBUS2

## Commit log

2021-01-07 Update silk
2021-01-14 Adding the schematic in pdf format
2021-02-04 Add examples

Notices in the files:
parts and their libraries:
SparkFun-Aesthetics: Licensing: Creative Commons ShareAlike 4.0 International - https://creativecommons.org/licenses/by-sa/4.0
SparkFun-Aesthetics: Released under the Creative Commons Attribution Share-Alike 4.0 License
SparkFun-Aesthetics: https://creativecommons.org/licenses/by-sa/4.0
